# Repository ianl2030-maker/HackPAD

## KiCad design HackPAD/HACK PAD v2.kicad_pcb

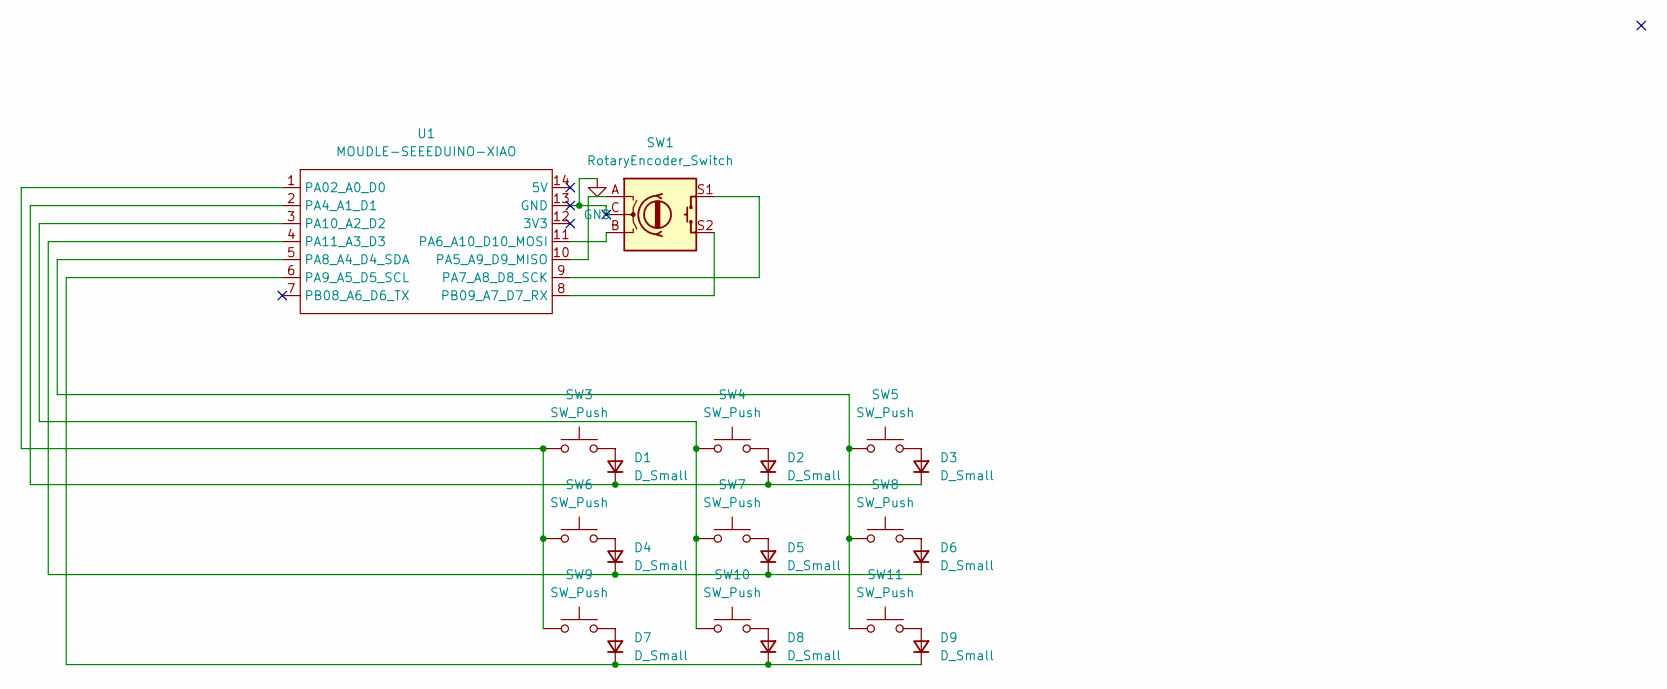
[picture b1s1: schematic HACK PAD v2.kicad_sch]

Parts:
D1, D2, D3, D4, D5, D6, D7, D8, D9: D_Small; D_SMA-SMB_Universal_Handsoldering
SW1: RotaryEncoder_Switch; RotaryEncoder_Alps_EC11E-Switch_Vertical_H20mm
SW3, SW4, SW5, SW6, SW7, SW8, SW9, SW10, SW11: SW_Push; SW_Cherry_MX_1.00u_PCB
U1: MOUDLE-SEEEDUINO-XIAO; XIAO-Generic-Hybrid-14P-2.54-21X17.8MM

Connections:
GND: SW1.C, U1.13 (GND)
unnamed: D1.2 (A), SW3.2
unnamed: D1.1 (K), D2.1 (K), D3.1 (K), U1.2 (PA4_A1_D1)
unnamed: D2.2 (A), SW4.2
unnamed: D3.2 (A), SW5.2
unnamed: D4.2 (A), SW6.2
unnamed: D4.1 (K), D5.1 (K), D6.1 (K), U1.4 (PA11_A3_D3)
unnamed: D5.2 (A), SW7.2
unnamed: D6.2 (A), SW8.2
unnamed: D7.2 (A), SW9.2
unnamed: D7.1 (K), D8.1 (K), D9.1 (K), U1.6 (PA9_A5_D5_SCL)
unnamed: D8.2 (A), SW10.2
unnamed: D9.2 (A), SW11.2
unnamed: SW3.1, SW6.1, SW9.1, U1.1 (PA02_A0_D0)
unnamed: SW1.A, U1.10 (PA5_A9_D9_MISO)
unnamed: SW1.B, U1.11 (PA6_A10_D10_MOSI)
unnamed: SW1.S1, U1.9 (PA7_A8_D8_SCK)
unnamed: SW5.1, SW8.1, SW11.1, U1.5 (PA8_A4_D4_SDA)
unnamed: SW4.1, SW7.1, SW10.1, U1.3 (PA10_A2_D2)
unnamed: SW1.S2, U1.8 (PB09_A7_D7_RX)

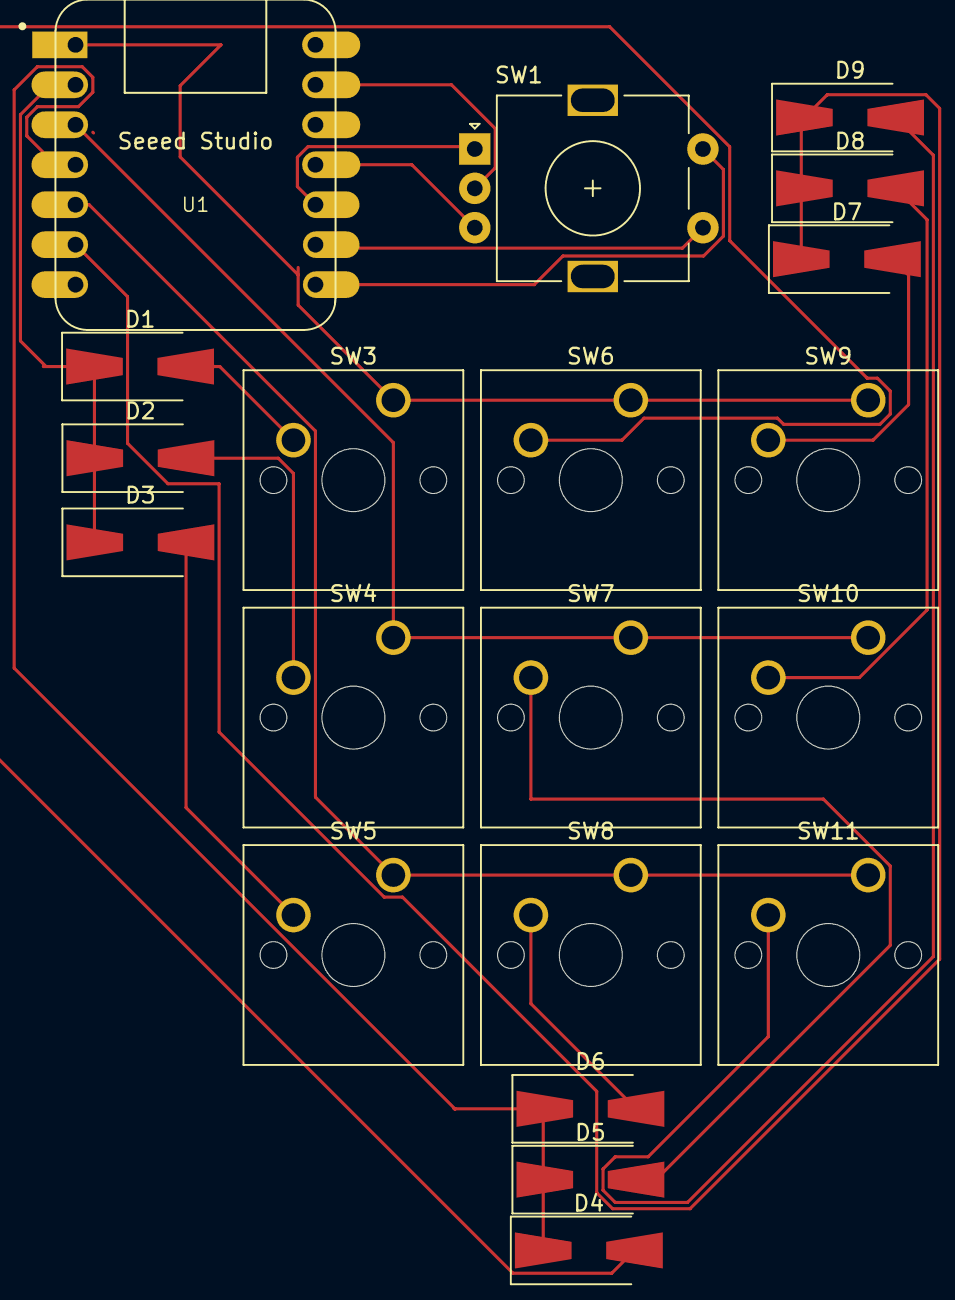
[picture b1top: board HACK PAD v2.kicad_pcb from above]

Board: 2 copper layers, 20 parts (0 on the bottom side), 20 nets.
